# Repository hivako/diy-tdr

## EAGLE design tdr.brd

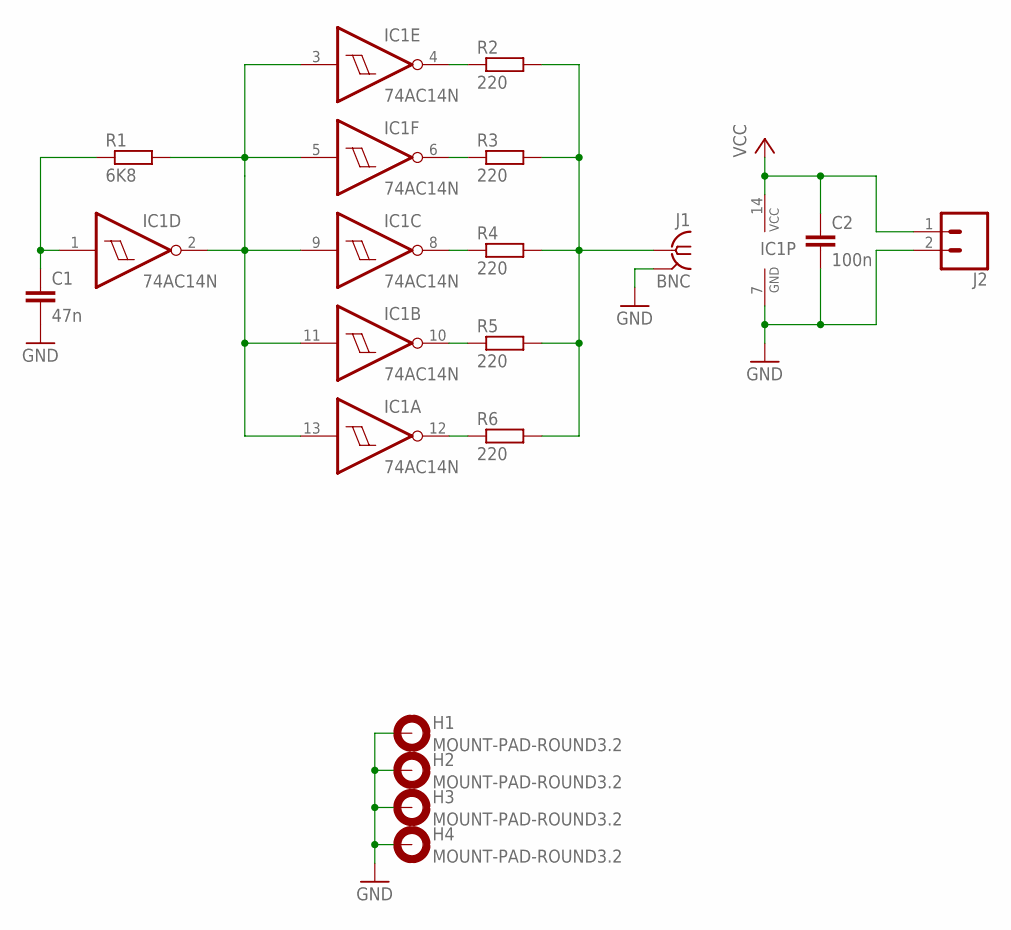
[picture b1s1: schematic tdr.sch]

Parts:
C1: 47n; C075-032X103
C2: 100n; C075-032X103
H1, H2, H3, H4: MOUNT-PAD-ROUND3.2; 3,2-PAD
IC1: 74AC14N; DIL14
J1: BNC; BNC_TYCO
J2: CONN_023.5MM; SCREWTERMINAL-3.5MM-2
R1: 6K8; 0207/10
R2, R3, R4, R5, R6: 220; 0207/10

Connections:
GND: C1.2, C2.2, H1.B3,2, H2.B3,2, H3.B3,2, H4.B3,2, IC1.7 (GND), J1.G (GND), J2.2
unnamed: C1.1, IC1.1 (I), R1.1
unnamed: IC1.2 (O), IC1.3 (I), IC1.5 (I), IC1.9 (I), IC1.11 (I), IC1.13 (I), R1.2
unnamed: IC1.4 (O), R2.1
unnamed: IC1.6 (O), R3.1
unnamed: IC1.8 (O), R4.1
unnamed: IC1.10 (O), R5.1
unnamed: IC1.12 (O), R6.1
unnamed: J1.C (1), R2.2, R3.2, R4.2, R5.2, R6.2
VCC: C2.1, IC1.14 (VCC), J2.1

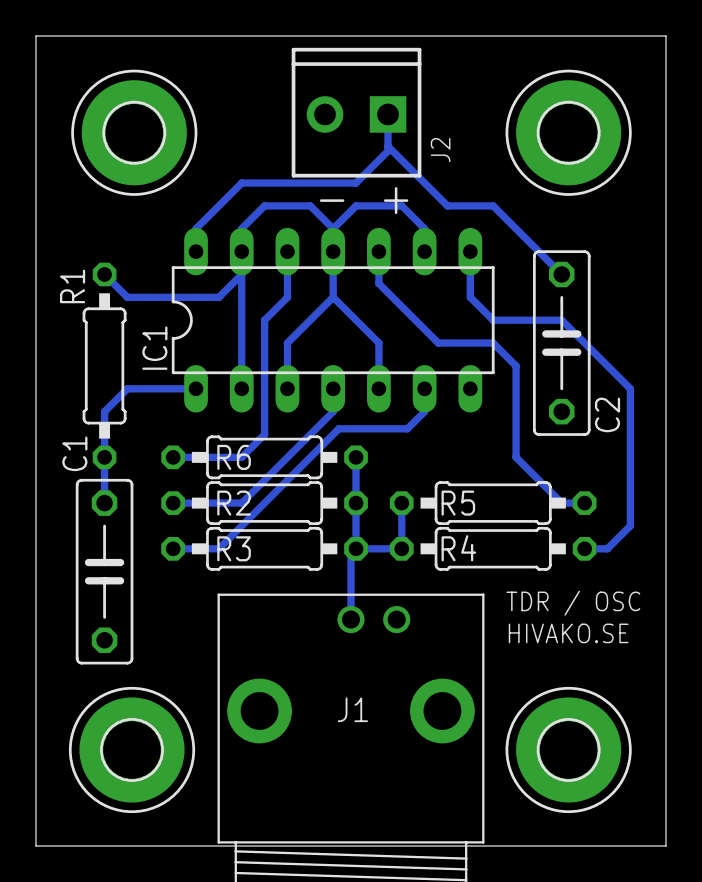
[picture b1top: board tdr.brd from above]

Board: 2 copper layers, 35.0 x 45.0 mm, 15 parts (0 on the bottom side), 10 nets.
